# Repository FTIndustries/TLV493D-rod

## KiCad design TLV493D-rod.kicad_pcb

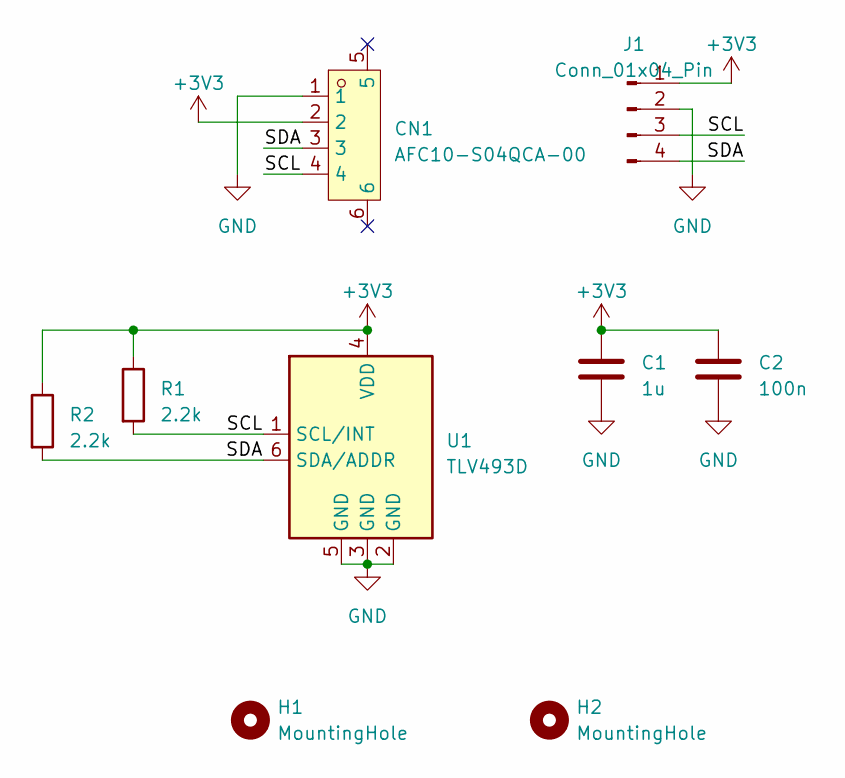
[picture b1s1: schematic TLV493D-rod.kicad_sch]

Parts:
C1: 1u; C_0603_1608Metric
C2: 100n; C_0402_1005Metric
CN1: AFC10-S04QCA-00; CONN-SMD_AFC10-S04QCA-00; LCSC Part C2764183
H1, H2: MountingHole; MountingHole_2.2mm_M2
J1: Conn_01x04_Pin; PinSocket_1x04_P2.54mm_Vertical
R1, R2: 2.2k; R_0402_1005Metric
U1: TLV493D; SOP-6_L3.0-W1.5-P0.95-LS2.5-BR

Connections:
+3V3: C1.1, C2.1, CN1.2, J1.1, R1.1, R2.1, U1.4 (VDD)
/SCL: CN1.4, J1.3, R1.2, U1.1 (SCL/INT)
/SDA: CN1.3, J1.4, R2.2, U1.6 (SDA/ADDR)
GND: C1.2, C2.2, CN1.1, J1.2, U1.2 (GND), U1.3 (GND), U1.5 (GND)

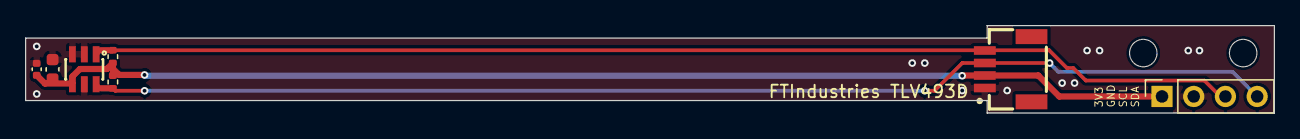
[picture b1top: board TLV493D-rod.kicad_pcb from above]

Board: 2 copper layers, 100.0 x 7.0 mm, 9 parts (0 on the bottom side), 4 nets.

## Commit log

2024-01-19 asdf
2024-01-26 add branding
2024-02-19 fix incorrect footprint
2024-04-16 revamp mounting, fix qwiic pinout
2024-05-10 gitignore
